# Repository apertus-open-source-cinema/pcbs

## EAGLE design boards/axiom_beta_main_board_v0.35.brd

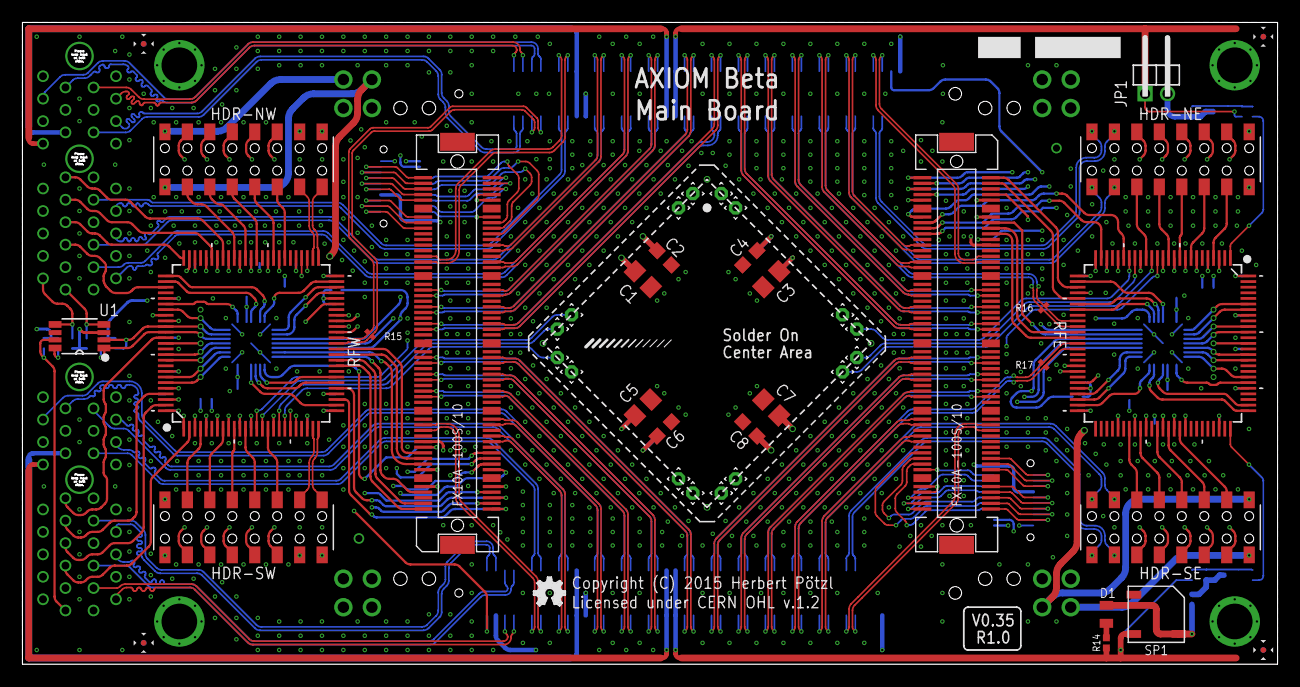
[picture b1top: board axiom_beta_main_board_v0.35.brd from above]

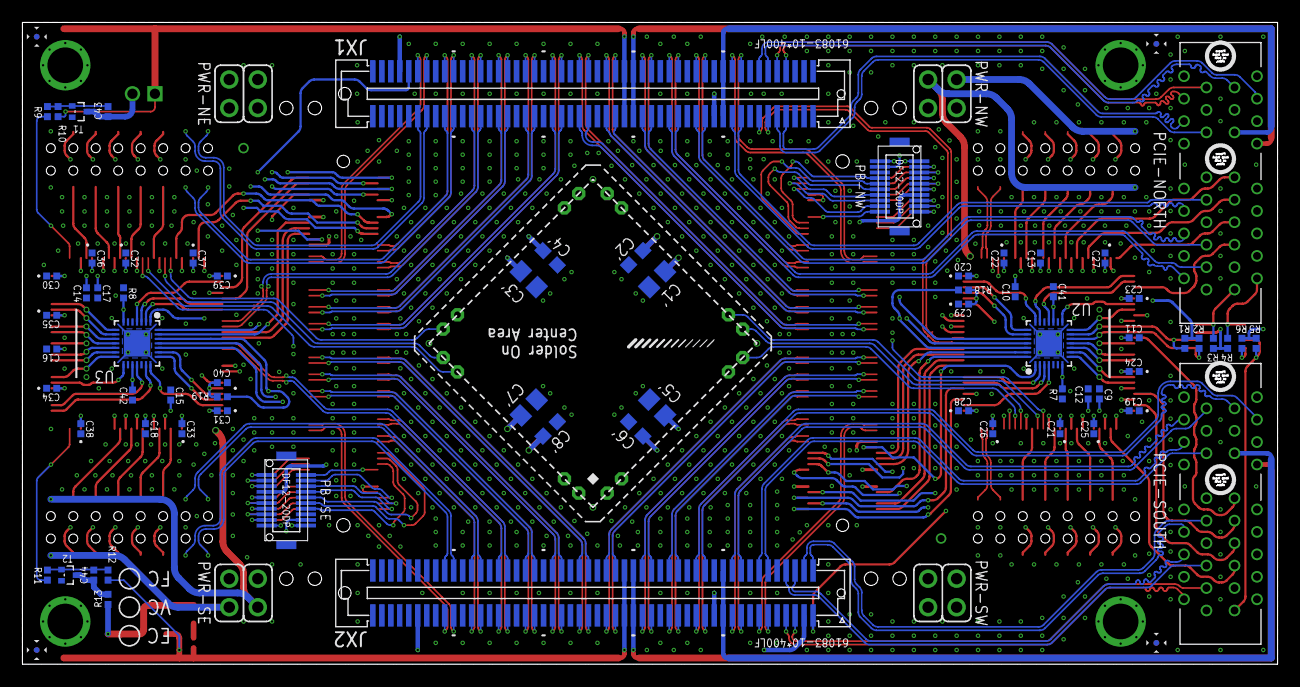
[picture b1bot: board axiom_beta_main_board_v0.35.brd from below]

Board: 4 copper layers, 111.8 x 57.1 mm, 113 parts (72 on the bottom side), 324 nets.

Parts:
C1, C1', C3, C3', C5, C5', C7, C7': 0805-A
C2, C2', C4, C4', C6, C6', C8, C8': 0603-A
C9, C10, C11, C12, C13, C14, C15, C16, C17, C18, C41, C42: 100n; 0402-B
C19, C20, C21, C22, C23, C24, C25, C26, C27, C28, C29, C30, C31, C32, C33, C34, C35, C36, C37, C38, C39, C40, C43, C44: 10n; 0402-B
D1: MICROMELF-R
HDR-NE: 62101621821
HDR-NW: 62101621821
HDR-SE: 62101621821
HDR-SW: 62101621821
JP1: 1X02M/90-S
LOGO1: OSHW_LOGO_FILLX0100-NT; OSHW_FILLX100_NOTEXT
PAD1, PAD2, PAD3, PAD4, PAD5, PAD6, PAD7, PAD8, PAD9, PAD10, PAD11, PAD12, PAD13, PAD14, PAD15, PAD16: PINPAD1.27MM; 1.2/0.6
PB-NW: DF12(XX)-20DP-0.5V
PB-SE: DF12(XX)-20DP-0.5V
PCIE-NORTH: PCIE-36-AXIOM-NOPEG; PCIE-36-NOPEG
PCIE-SOUTH: PCIE-36-AXIOM-NOPEG; PCIE-36-NOPEG
PWR-NE: PINHD-2X02_2.54; 2X02
PWR-NW: PINHD-2X02_2.54; 2X02
PWR-SE: PINHD-2X02_2.54; 2X02
PWR-SW: PINHD-2X02_2.54; 2X02
R1, R2, R3, R4, R5, R6: 4k7; 0402-B
R7, R8: 50R; 0402-B
R9, R10, R11, R12, R13, R14: 0402-B
R15, R16, R17: 100R; 0201-B
R18, R19: 10k; 0402-B
RFE: MACHXO2-100; MACHXO2-100TQFP
RFW: MACHXO2-100; MACHXO2-100TQFP
SP1: KSSG23J12
T1, T2: NX3008NBKT; SOT416
U1: PCA9540BDP; SOP65P490X300-8N
U2, U3: PIC16F1718-I/MV; QFN40P400X400X55-29N
X-EAST: FX10-100/10S; FX10A-100S/10
X-WEST: FX10-100/10S; FX10A-100S/10
ZED1: µZ-FCI-NOHOLES-R; µZ-NOHOLES-R

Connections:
!E_RESET!: U3.1, X-EAST.19
!SS!_E: RFE.27, U3.4
!SS!_W: RFW.27, U2.4
!W_RESET!: U2.1, X-WEST.19
A_!RST: PB-NW.2, R18.2, U2.26
A_SCL: PB-NW.1, U2.24
A_SDA: PB-NW.3, U2.25
BANK13_00_N: PCIE-NORTH.B17, ZED1.89
BANK13_00_P: PCIE-NORTH.B16, ZED1.87
BANK13_01_N: R15.2, RFW.38, ZED1.90
BANK13_01_P: R15.1, RFW.39, ZED1.88
BANK13_02_N: PCIE-NORTH.A16, ZED1.93
BANK13_02_P: PCIE-NORTH.A17, ZED1.91
BANK13_03_N: PCIE-NORTH.A14, ZED1.94
BANK13_03_P: PCIE-NORTH.A13, ZED1.92
BANK13_04_N: PCIE-SOUTH.A6, ZED1.195
BANK13_04_P: PCIE-SOUTH.A5, ZED1.193
BANK13_05_N: PCIE-SOUTH.A3, ZED1.196
BANK13_05_P: PCIE-SOUTH.A2, ZED1.194
BANK13_06_N: PCIE-SOUTH.A8, ZED1.199
BANK13_06_P: PCIE-SOUTH.A9, ZED1.197
BANK13_SE_0: R7.1, RFW.88, U2.7, ZED1.200
B_!RST: PB-SE.2, R19.2, U3.26
B_SCL: PB-SE.1, U3.24
B_SDA: PB-SE.3, U3.25
CSO_NE_V: C3.1, C3'.1, C4.1, C4'.1, PAD2.1, ZED1.7
CSO_NW_V: C1.1, C1'.1, C2.1, C2'.1, PAD15.1, PWR-NW.1
CSO_SE_V: C7.1, C7'.1, C8.1, C8'.1, PAD7.1, PWR-SE.1
CSO_SW_V: C5.1, C5'.1, C6.1, C6'.1, PAD10.1, ZED1.112
C_CK_E: PAD5.1, RFE.18
C_CK_W: PAD13.1, RFW.18
C_EN_E: PAD3.1, RFE.14
C_EN_W: PAD11.1, RFW.14
C_SI_E: PAD4.1, RFE.19
C_SI_W: PAD12.1, RFW.19
C_SO_E: PAD6.1, RFE.15
C_SO_W: PAD14.1, RFW.15
DONE_E: RFE.76, U3.20
DONE_W: RFW.76, U2.20
E_EN: RFE.20, X-EAST.14
E_I2C_EN: U3.27, X-EAST.13
E_I2C_V: PWR-NE.1, X-EAST.11
E_SCK: RFE.21, X-EAST.12
E_SCL: RFE.36, X-EAST.15
E_SDA: RFE.37, X-EAST.17
E_SDI: RFE.24, X-EAST.16
E_SDO: RFE.25, X-EAST.18
E_SPI_V: PWR-NE.3, X-EAST.21
E_VE_CV: PB-SE.19, X-EAST.90
E_VE_OV: PB-SE.10, X-EAST.93
E_VE_UV: PB-SE.12, X-EAST.91
GND: C1.2, C1'.2, C2.2, C2'.2, C3.2, C3'.2, C4.2, C4'.2, C5.2, C5'.2, C6.2, C6'.2, C7.2, C7'.2, C8.2, C8'.2, C9.2, C10.2, C11.2, C12.2, C13.2, C14.2, C15.2, C16.2, C17.2, C18.2, C19.2, C20.2, C21.2, C22.2, C23.2, C24.2, C25.2, C26.2, C27.2, C28.2, C29.2, C30.2, C31.2, C32.2, C33.2, C34.2, C35.2, C36.2, C37.2, C38.2, C39.2, C40.2, C41.2, C42.2, HDR-NE.1, HDR-NE.2, HDR-SW.1, HDR-SW.2, PAD1.1, PAD8.1, PAD9.1, PAD16.1, PB-NW.5, PB-SE.5, PCIE-NORTH.A1, PCIE-NORTH.A4, PCIE-NORTH.A7, PCIE-NORTH.A10, PCIE-NORTH.A12, PCIE-NORTH.A15, PCIE-NORTH.A18, PCIE-NORTH.B15, PCIE-NORTH.B18, PCIE-SOUTH.A1, PCIE-SOUTH.A4, PCIE-SOUTH.A7, PCIE-SOUTH.A10, PCIE-SOUTH.A12, PCIE-SOUTH.A15, PCIE-SOUTH.A18, PCIE-SOUTH.B15, PCIE-SOUTH.B18, R7.2, R8.2, RFE.6, RFE.22, RFE.33, RFE.44, RFE.56, RFE.72, RFE.79, RFE.92, RFW.6, RFW.22, RFW.33, RFW.44, RFW.56, RFW.72, RFW.79, RFW.92, T1.2, U1.6, U2.5, U2.16, U2.29, U3.5, U3.16, U3.29, X-EAST.5, X-EAST.20, X-EAST.23, X-EAST.26, X-EAST.29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
INITN_E: RFE.77, U3.18
INITN_W: RFW.77, U2.18
IO_SCL: RFE.86, U3.12
IO_SDA: RFE.85, U3.13
JTAGENB_E: RFE.82, U3.14
JTAGENB_W: RFW.82, U2.14
JTAG_V: PWR-SW.3, X-WEST.21
JX1_00_N: X-EAST.27, ZED1.13
JX1_00_P: X-EAST.25, ZED1.11
JX1_01_N: HDR-NE.13, ZED1.14
JX1_01_P: HDR-NE.15, ZED1.12
JX1_02_N: X-EAST.24, ZED1.19
JX1_02_P: X-EAST.22, ZED1.17
JX1_03_N: HDR-NE.14, ZED1.20
JX1_03_P: HDR-NE.16, ZED1.18
JX1_04_N: X-EAST.30, ZED1.25
JX1_04_P: X-EAST.28, ZED1.23
JX1_05_N: R16.2, RFE.35, ZED1.26
JX1_05_P: R16.1, RFE.34, ZED1.24
JX1_06_N: X-EAST.36, ZED1.31
JX1_06_P: X-EAST.34, ZED1.29
JX1_07_N: X-EAST.35, ZED1.32
JX1_07_P: X-EAST.33, ZED1.30
JX1_08_N: X-EAST.42, ZED1.37
JX1_08_P: X-EAST.40, ZED1.35
JX1_09_N: X-EAST.41, ZED1.38
JX1_09_P: X-EAST.39, ZED1.36
JX1_10_N: X-EAST.48, ZED1.43
JX1_10_P: X-EAST.46, ZED1.41
JX1_11_N: X-EAST.47, ZED1.44
JX1_11_P: X-EAST.45, ZED1.42
JX1_12_N: X-WEST.56, ZED1.49
JX1_12_P: X-WEST.54, ZED1.47
JX1_13_N: X-WEST.55, ZED1.50
JX1_13_P: X-WEST.53, ZED1.48
JX1_14_N: X-WEST.62, ZED1.55
JX1_14_P: X-WEST.60, ZED1.53
JX1_15_N: X-WEST.61, ZED1.56
JX1_15_P: X-WEST.59, ZED1.54
JX1_16_N: X-WEST.68, ZED1.63
JX1_16_P: X-WEST.66, ZED1.61
JX1_17_N: X-WEST.67, ZED1.64
JX1_17_P: X-WEST.65, ZED1.62
JX1_18_N: X-WEST.74, ZED1.69
JX1_18_P: X-WEST.72, ZED1.67
JX1_19_N: PCIE-NORTH.A3, ZED1.70
JX1_19_P: PCIE-NORTH.A2, ZED1.68
JX1_20_N: X-WEST.80, ZED1.75
JX1_20_P: X-WEST.78, ZED1.73
JX1_21_N: PCIE-NORTH.A6, ZED1.76
JX1_21_P: PCIE-NORTH.A5, ZED1.74
JX1_22_N: X-WEST.75, ZED1.83
JX1_22_P: X-WEST.73, ZED1.81
JX1_23_N: PCIE-NORTH.A9, ZED1.84
JX1_23_P: PCIE-NORTH.A8, ZED1.82
JX1_SE_0: R8.1, RFE.88, U3.7, ZED1.9
JX2_00_N: HDR-SE.14, ZED1.119
JX2_00_P: HDR-SE.16, ZED1.117
JX2_01_N: X-EAST.73, ZED1.120
JX2_01_P: X-EAST.75, ZED1.118
JX2_02_N: HDR-SE.13, ZED1.125
JX2_02_P: HDR-SE.15, ZED1.123
JX2_03_N: X-EAST.78, ZED1.126
JX2_03_P: X-EAST.80, ZED1.124
JX2_04_N: R17.1, RFE.38, ZED1.131
JX2_04_P: R17.2, RFE.39, ZED1.129
JX2_05_N: X-EAST.72, ZED1.132
JX2_05_P: X-EAST.74, ZED1.130
JX2_06_N: X-EAST.65, ZED1.137
JX2_06_P: X-EAST.67, ZED1.135
JX2_07_N: X-EAST.66, ZED1.138
JX2_07_P: X-EAST.68, ZED1.136
JX2_08_N: X-EAST.59, ZED1.143
JX2_08_P: X-EAST.61, ZED1.141
JX2_09_N: X-EAST.60, ZED1.144
JX2_09_P: X-EAST.62, ZED1.142
JX2_10_N: X-EAST.53, ZED1.149
JX2_10_P: X-EAST.55, ZED1.147
JX2_11_N: X-EAST.54, ZED1.150
JX2_11_P: X-EAST.56, ZED1.148
JX2_12_N: X-WEST.45, ZED1.155
JX2_12_P: X-WEST.47, ZED1.153
JX2_13_N: X-WEST.46, ZED1.156
JX2_13_P: X-WEST.48, ZED1.154
JX2_14_N: X-WEST.39, ZED1.163
JX2_14_P: X-WEST.41, ZED1.161
JX2_15_N: X-WEST.40, ZED1.164
JX2_15_P: X-WEST.42, ZED1.162
JX2_16_N: X-WEST.33, ZED1.169
JX2_16_P: X-WEST.35, ZED1.167
JX2_17_N: X-WEST.34, ZED1.170
JX2_17_P: X-WEST.36, ZED1.168
JX2_18_N: PCIE-SOUTH.B17, ZED1.175
JX2_18_P: PCIE-SOUTH.B16, ZED1.173
JX2_19_N: X-WEST.28, ZED1.176
JX2_19_P: X-WEST.30, ZED1.174
JX2_20_N: PCIE-SOUTH.A17, ZED1.183
JX2_20_P: PCIE-SOUTH.A16, ZED1.181
JX2_21_N: X-WEST.22, ZED1.184
JX2_21_P: X-WEST.24, ZED1.182
JX2_22_N: PCIE-SOUTH.A13, ZED1.189
JX2_22_P: PCIE-SOUTH.A14, ZED1.187
JX2_23_N: X-WEST.25, ZED1.190
JX2_23_P: X-WEST.27, ZED1.188
unnamed: C43.2, JP1.2, T1.3
unnamed: C44.2, R13.1, T2.3
unnamed: D1.C, R14.1
unnamed: D1.A, R13.2, SP1.2
unnamed: C43.1, R9.2, R10.2, T1.1
unnamed: C44.1, R11.1, R12.2, T2.1
N_CHK_V: PB-NW.14, X-WEST.92
N_I2C_EN: U3.28, X-EAST.7
N_I2C_V: PWR-NE.4, X-EAST.9
N_IO0: R9.1, RFE.1
N_SCK: RFE.42, X-EAST.2
N_SCL: RFE.28, X-EAST.1
N_SDA: RFE.30, X-EAST.3
N_SDI: RFE.29, X-EAST.6
N_SDO: RFE.43, X-EAST.4
N_SPI_EN: RFE.45, X-EAST.8
N_SPI_V: PWR-NE.2, X-EAST.10
N_VE_CV: PB-NW.17, X-WEST.96
N_VE_OV: PB-NW.8, X-WEST.95
N_VE_RS: PB-NW.7, X-WEST.88
N_VE_UV: PB-NW.20, X-WEST.85
N_VN_CV: PB-NW.15, X-WEST.98
N_VN_OV: PB-NW.6, X-WEST.97
N_VN_RS: PB-NW.11, X-WEST.86
N_VN_UV: PB-NW.18, X-WEST.87
N_VW_CV: PB-NW.13, X-WEST.100
N_VW_OV: PB-NW.4, X-WEST.99
N_VW_RS: PB-NW.9, X-WEST.84
N_VW_UV: PB-NW.16, X-WEST.89
PB22B_E: RFE.47, U3.23
PB22B_W: RFW.47, U2.23
PCIE_I2C_V: PCIE-NORTH.B3, PCIE-SOUTH.B3, R3.1, R4.1, R5.1, R6.1, U1.3, ZED1.198
PCIE_N_5V: PCIE-NORTH.B12, ZED1.59, ZED1.60
PCIE_N_IO0: PCIE-NORTH.B4, RFW.83
PCIE_N_IO1: PCIE-NORTH.B5, RFW.78
PCIE_N_IO2: PCIE-NORTH.B6, RFW.74
PCIE_N_IO3: PCIE-NORTH.B7, RFW.75
PCIE_N_IO4: PCIE-NORTH.B8, RFW.71
PCIE_N_IO5: PCIE-NORTH.B9, RFW.70
PCIE_N_IO6: PCIE-NORTH.B10, RFW.69
PCIE_N_IO7: PCIE-NORTH.B11, RFW.68
PCIE_N_SCL: PCIE-NORTH.B2, R4.2, U1.5
PCIE_N_SDA: PCIE-NORTH.B1, R3.2, U1.4
PCIE_N_V: PCIE-NORTH.B13, ZED1.79, ZED1.80
PCIE_N_VCCIO: PCIE-NORTH.B14, ZED1.78
PCIE_SCL: R2.2, RFW.86, U1.1, U2.12
PCIE_SDA: R1.2, RFW.85, U1.2, U2.13
PCIE_S_5V: PCIE-SOUTH.B12, ZED1.159, ZED1.160
PCIE_S_IO0: PCIE-SOUTH.B4, RFW.1
PCIE_S_IO1: PCIE-SOUTH.B5, RFW.2
PCIE_S_IO2: PCIE-SOUTH.B6, RFW.98
PCIE_S_IO3: PCIE-SOUTH.B7, RFW.99
PCIE_S_IO4: PCIE-SOUTH.B8, RFW.96
PCIE_S_IO5: PCIE-SOUTH.B9, RFW.97
PCIE_S_IO6: PCIE-SOUTH.B10, RFW.84
PCIE_S_IO7: PCIE-SOUTH.B11, RFW.87
PCIE_S_SCL: PCIE-SOUTH.B2, R6.2, U1.8
PCIE_S_SDA: PCIE-SOUTH.B1, R5.2, U1.7
PCIE_S_V: PCIE-SOUTH.B13, ZED1.179, ZED1.180
PCIE_S_VCCIO: PCIE-SOUTH.B14, ZED1.178
PEX_N_V: JP1.1, R10.1, ZED1.57, ZED1.58
PEX_S_V: R12.1, R14.2, SP1.1, ZED1.157, ZED1.158
PROGRAMN_E: RFE.81, U3.15
PROGRAMN_W: RFW.81, U2.15
RFAB_E_V: C14.1, C15.1, C30.1, C31.1, PWR-SE.3, RFE.50, RFE.100
RFAB_W_V: C9.1, C10.1, C19.1, C20.1, PWR-NW.3, RFW.50, RFW.100
SCK_E: RFE.31, U3.3
SCK_W: RFW.31, U2.3
SDI_E: RFE.49, U3.21
SDI_W: RFW.49, U2.21
SDO_E: RFE.32, U3.2
SDO_W: RFW.32, U2.2
SH_NE_IO0: HDR-NE.4, RFE.4
SH_NE_IO1: HDR-NE.3, RFE.3
SH_NE_IO2: HDR-NE.6, RFE.8
SH_NE_IO3: HDR-NE.5, RFE.7
SH_NE_IO4: HDR-NE.8, RFE.10
SH_NE_IO5: HDR-NE.7, RFE.9
SH_NE_IO6: HDR-NE.10, RFE.12
SH_NE_IO7: HDR-NE.9, RFE.13
SH_NE_IO8: HDR-NE.12, RFE.16
SH_NE_IO9: HDR-NE.11, RFE.17
SH_NW_IO0: HDR-NW.4, RFW.67
SH_NW_IO1: HDR-NW.3, RFW.66
SH_NW_IO2: HDR-NW.6, RFW.65
SH_NW_IO3: HDR-NW.5, RFW.64
SH_NW_IO4: HDR-NW.8, RFW.63
SH_NW_IO5: HDR-NW.7, RFW.62
SH_NW_IO6: HDR-NW.10, RFW.60
SH_NW_IO7: HDR-NW.9, RFW.59
SH_NW_IO8: HDR-NW.12, RFW.58
SH_NW_IO9: HDR-NW.11, RFW.57
SH_NW_V: HDR-NW.2, PWR-NW.4
SH_NW_VIO: C11.1, C12.1, C13.1, C21.1, C22.1, C23.1, C24.1, C25.1, C26.1, C27.1, C28.1, C29.1, C41.1, HDR-NW.1, PWR-NW.2, R1.1, R2.1, R18.1, RFW.5, RFW.11, RFW.23, RFW.26, RFW.46, RFW.55, RFW.73, RFW.80, RFW.93, U2.17
SH_SE_IO0: HDR-SE.4, RFE.67
SH_SE_IO1: HDR-SE.3, RFE.66
SH_SE_IO2: HDR-SE.6, RFE.65
SH_SE_IO3: HDR-SE.5, RFE.64
SH_SE_IO4: HDR-SE.8, RFE.63
SH_SE_IO5: HDR-SE.7, RFE.62
SH_SE_IO6: HDR-SE.10, RFE.60
SH_SE_IO7: HDR-SE.9, RFE.59
SH_SE_IO8: HDR-SE.12, RFE.58
SH_SE_IO9: HDR-SE.11, RFE.57
SH_SE_V: HDR-SE.2, PWR-SE.4
SH_SE_VIO: C16.1, C17.1, C18.1, C32.1, C33.1, C34.1, C35.1, C36.1, C37.1, C38.1, C39.1, C40.1, C42.1, HDR-SE.1, PWR-SE.2, R19.1, RFE.5, RFE.11, RFE.23, RFE.26, RFE.46, RFE.55, RFE.73, RFE.80, RFE.93, U3.17
SH_SW_IO0: HDR-SW.4, RFW.4
SH_SW_IO1: HDR-SW.3, RFW.3
SH_SW_IO2: HDR-SW.6, RFW.8
SH_SW_IO3: HDR-SW.5, RFW.7
SH_SW_IO4: HDR-SW.8, RFW.10
SH_SW_IO5: HDR-SW.7, RFW.9
SH_SW_IO6: HDR-SW.10, RFW.12
SH_SW_IO7: HDR-SW.9, RFW.13
SH_SW_IO8: HDR-SW.12, RFW.16
SH_SW_IO9: HDR-SW.11, RFW.17
SN_E: RFE.48, U3.22
SN_W: RFW.48, U2.22
S_CHK_V: PB-SE.14, X-EAST.92
S_I2C_EN: U2.28, X-WEST.7
S_I2C_V: PWR-SW.4, X-WEST.9
S_IO0: R11.2, RFE.75
S_SCK: RFW.28, X-WEST.2
S_SCL: RFW.34, X-WEST.1
S_SDA: RFW.35, X-WEST.3
S_SDI: RFW.30, X-WEST.6
S_SDO: RFW.29, X-WEST.4
S_SPI_EN: RFW.45, X-WEST.8
S_SPI_V: PWR-SW.2, X-WEST.10
S_VE_CV: PB-SE.13, X-EAST.100
S_VE_OV: PB-SE.4, X-EAST.99
S_VE_RS: PB-SE.9, X-EAST.84
S_VE_UV: PB-SE.16, X-EAST.89
S_VS_CV: PB-SE.15, X-EAST.98
S_VS_OV: PB-SE.6, X-EAST.97
S_VS_RS: PB-SE.11, X-EAST.86
S_VS_UV: PB-SE.18, X-EAST.87
S_VW_CV: PB-SE.17, X-EAST.96
S_VW_OV: PB-SE.8, X-EAST.95
S_VW_RS: PB-SE.7, X-EAST.88
S_VW_UV: PB-SE.20, X-EAST.85
TCK: RFW.43, X-WEST.12
TCK_E: RFE.91, U3.10
TCK_W: RFW.91, U2.10
TDI: RFW.41, X-WEST.16
TDI_E: RFE.94, U3.9
TDI_W: RFW.94, U2.9
TDO: RFW.40, X-WEST.18
TDO_E: RFE.95, U3.8
TDO_W: RFW.95, U2.8
TMS: RFW.42, X-WEST.14
TMS_E: RFE.90, U3.11
TMS_W: RFW.90, U2.11
W_I2C_EN: U2.27, X-WEST.13
W_I2C_V: PWR-SW.1, X-WEST.11
W_SCL: RFW.36, X-WEST.15
W_SDA: RFW.37, X-WEST.17
W_VW_CV: PB-NW.19, X-WEST.90
W_VW_OV: PB-NW.10, X-WEST.93
W_VW_UV: PB-NW.12, X-WEST.91
XX1_N: HDR-NW.13, RFW.52
XX1_P: HDR-NW.15, RFW.51
XX2_N: HDR-NW.14, RFW.54
XX2_P: HDR-NW.16, RFW.53
XX3_N: HDR-SW.16, RFW.25
XX3_P: HDR-SW.14, RFW.24
XX4_N: HDR-SW.15, RFW.21
XX4_P: HDR-SW.13, RFW.20

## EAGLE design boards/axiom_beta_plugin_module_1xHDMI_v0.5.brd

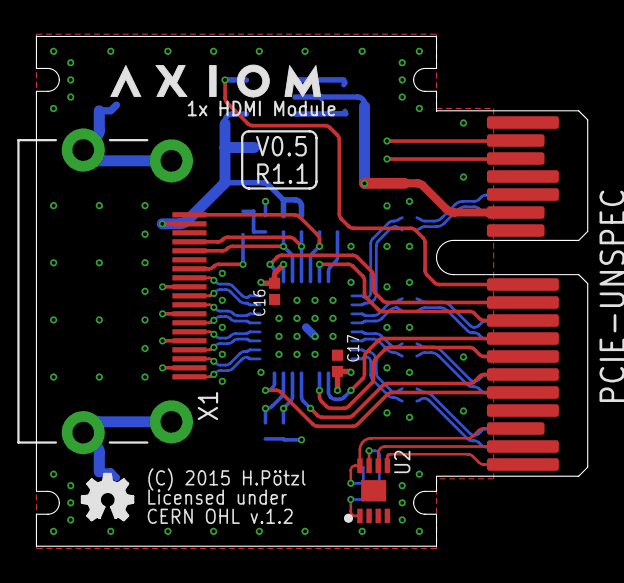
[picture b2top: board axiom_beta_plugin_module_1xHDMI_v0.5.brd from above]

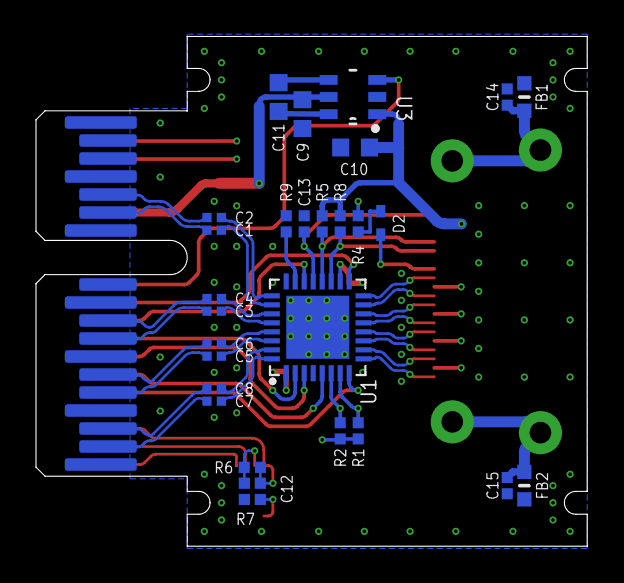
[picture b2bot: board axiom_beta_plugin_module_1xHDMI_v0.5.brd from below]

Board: 4 copper layers, 30.6 x 28.3 mm, 35 parts (28 on the bottom side), 50 nets.

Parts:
C1, C2, C3, C4, C5, C6, C7, C8: 100n; 0402-C
C9, C10, C11: 0603-B
C12: 0402-B
C13: 1-10n; 0402-B
C14, C15: 10n; 0402-B
C16, C17: 100n; 0402-B
D2: SOD523
FB1, FB2: _0603MP
LOGO2: OSHW_LOGO_FILLX0100-NT; OSHW_FILLX100_NOTEXT
PCIE-UNSPEC: PCIE-36-AXIOM
R1, R2, R5, R8: 2k2; 0402-B
R4, R6, R7: 0402-B
R9: 12k4; 0402-B
U1: PTN3363; HVQFN32
U2: BR24G04NUX; DFN200X300X100-9N
U3: REG710-DBV; DBV
U$1: AXIOM_LOGO459X70; AXIOM_LOGO_459X70
X1: HDMI-10029449; 10029449-X01XLF

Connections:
3V3: C9.1, C16.1, C17.1, PCIE-UNSPEC.B13, R1.1, R2.1, R4.1, U1.1, U1.18, U3.5
5V0: C10.1, R5.1, R8.1, U3.1, X1.18
!OE!: PCIE-UNSPEC.B10, U1.17
CLOCK_N: U1.16, X1.12
CLOCK_P: U1.15, X1.10
DATA0_N: U1.14, X1.9
DATA0_P: U1.13, X1.7
DATA1_N: U1.12, X1.6
DATA1_P: U1.11, X1.4
DATA2_N: U1.10, X1.3
DATA2_P: U1.9, X1.1
DDC_EN: PCIE-UNSPEC.B9, U1.22
DDET: PCIE-UNSPEC.B7, U1.3
EN: PCIE-UNSPEC.B11, U3.3
EQ0: PCIE-UNSPEC.B5, U1.8
EQ1: PCIE-UNSPEC.B8, U1.2
GND: C9.2, C10.2, C12.2, C13.2, C14.2, C15.2, C16.2, C17.2, FB1.2, FB2.2, PCIE-UNSPEC.A1, PCIE-UNSPEC.A4, PCIE-UNSPEC.A7, PCIE-UNSPEC.A10, PCIE-UNSPEC.A12, PCIE-UNSPEC.A15, PCIE-UNSPEC.A18, PCIE-UNSPEC.B15, PCIE-UNSPEC.B18, R7.2, R9.2, U1.24, U1.EP, U2.1, U2.2, U2.3, U2.4, U2.EP, U3.2, X1.2, X1.5, X1.8, X1.11, X1.17
HDMI_CEC: D2.C, X1.13
HDMI_HP: C13.1, U1.21, X1.19
HDMI_SCL: R8.2, U1.19, X1.15
HDMI_SDA: R5.2, U1.20, X1.16
I2C_V: C12.1, PCIE-UNSPEC.B3, R6.1, U2.8
IHP: PCIE-UNSPEC.B6, U1.5
IN_D1_N: C2.1, U1.25
IN_D1_P: C1.1, U1.26
IN_D2_N: C4.1, U1.27
IN_D2_P: C3.1, U1.28
IN_D3_N: C6.1, U1.29
IN_D3_P: C5.1, U1.30
IN_D4_N: C8.1, U1.31
IN_D4_P: C7.1, U1.32
ISCL: PCIE-UNSPEC.B16, R1.2, U1.7
ISDA: PCIE-UNSPEC.B17, R2.2, U1.6
LVDS_0_N: C8.2, PCIE-UNSPEC.A3
LVDS_0_P: C7.2, PCIE-UNSPEC.A2
LVDS_1_N: C6.2, PCIE-UNSPEC.A6
LVDS_1_P: C5.2, PCIE-UNSPEC.A5
LVDS_2_N: C4.2, PCIE-UNSPEC.A9
LVDS_2_P: C3.2, PCIE-UNSPEC.A8
LVDS_3_N: C2.2, PCIE-UNSPEC.A14
LVDS_3_P: C1.2, PCIE-UNSPEC.A13
unnamed: C11.1, U3.6
unnamed: C11.2, U3.4
unnamed: C14.1, FB1.1, X1.Z1, X1.Z2
unnamed: R6.2, R7.1, U2.7
unnamed: C15.1, FB2.1, X1.Z3, X1.Z4
unnamed: R9.1, U1.23
unnamed: D2.A, R4.2
SCL: PCIE-UNSPEC.B2, U2.6
SDA: PCIE-UNSPEC.B1, U2.5

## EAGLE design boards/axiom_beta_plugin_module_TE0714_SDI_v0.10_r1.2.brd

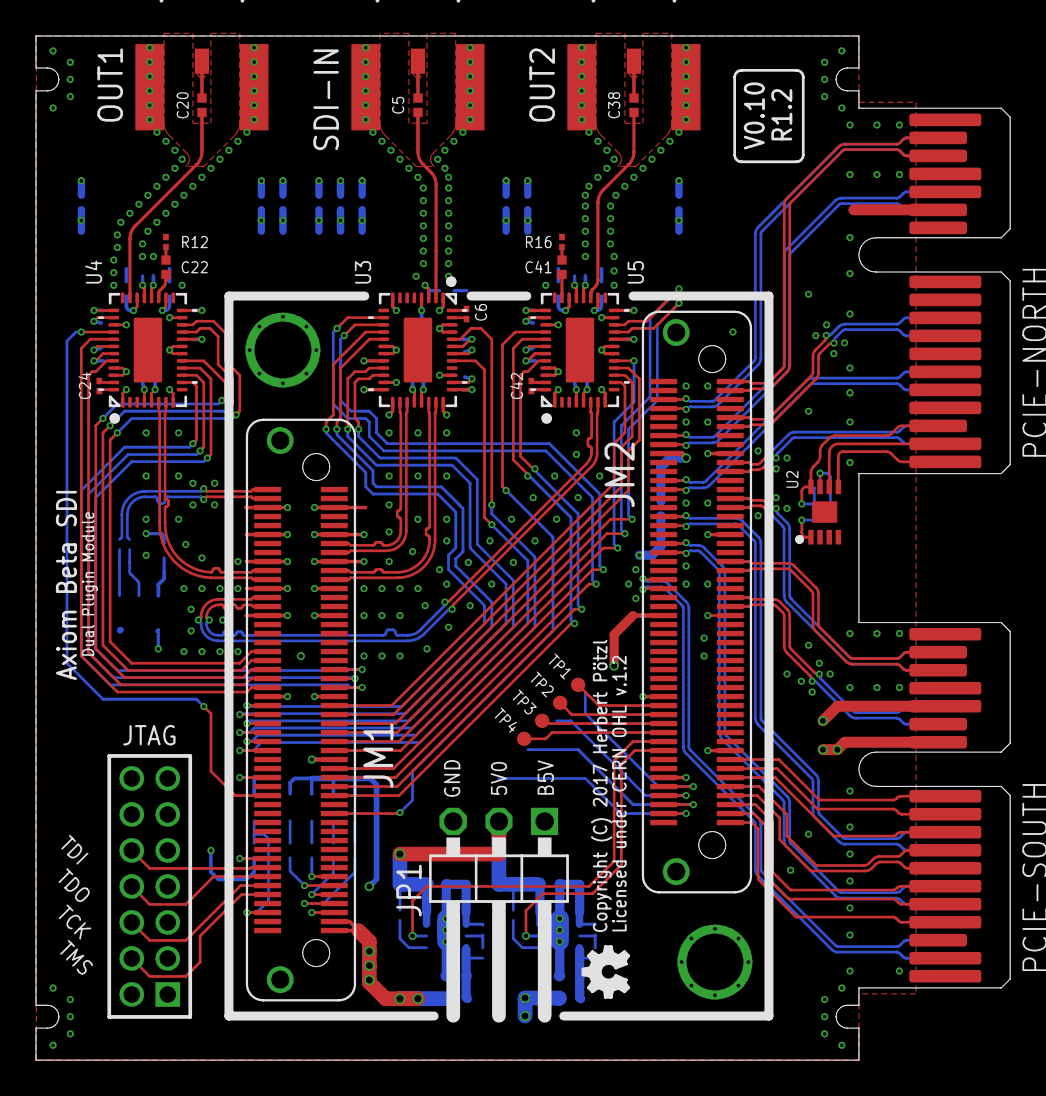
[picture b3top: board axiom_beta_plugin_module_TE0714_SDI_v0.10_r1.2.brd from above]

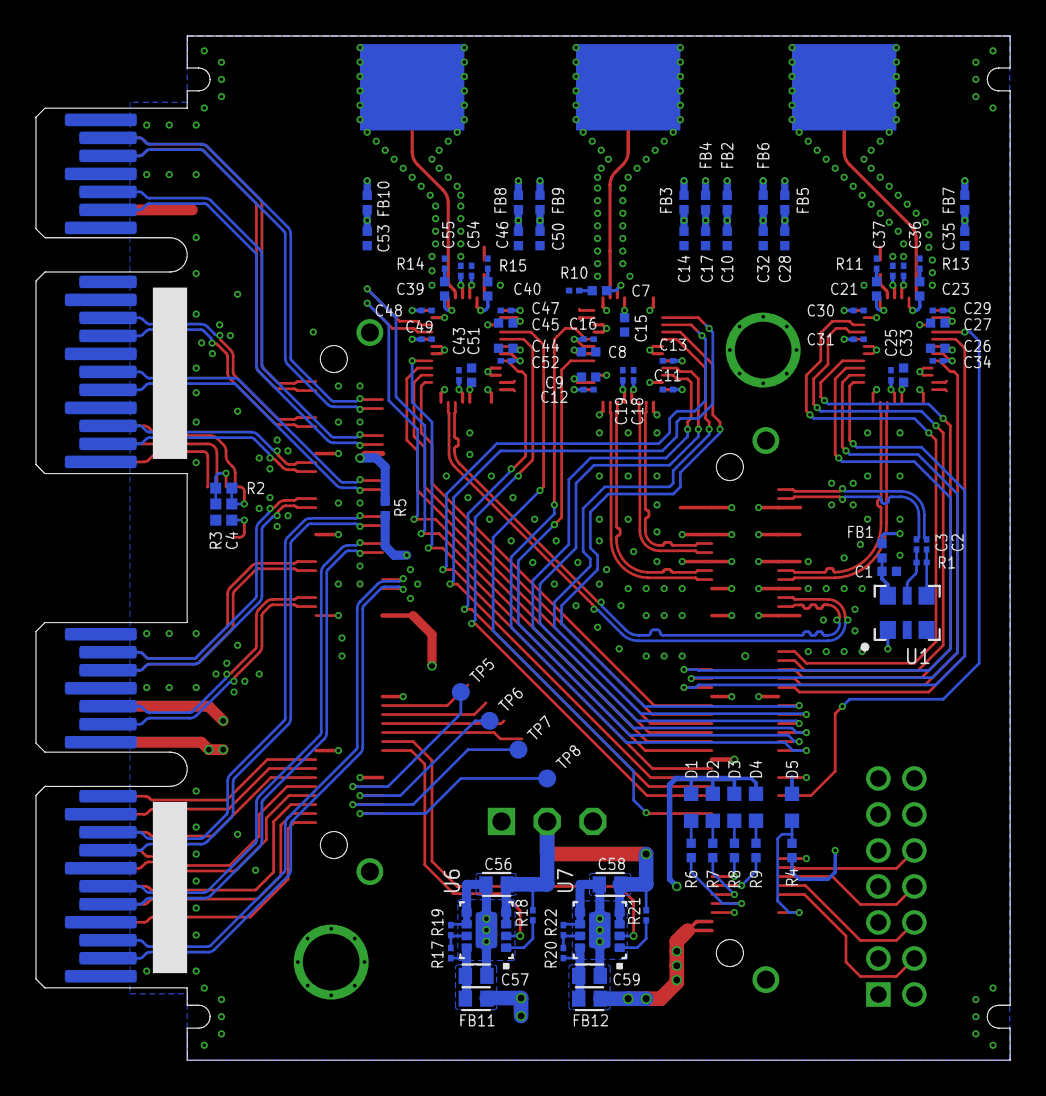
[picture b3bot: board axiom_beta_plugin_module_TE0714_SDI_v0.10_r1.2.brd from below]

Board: 4 copper layers, 54.1 x 56.9 mm, 123 parts (95 on the bottom side), 156 nets.

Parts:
C1: 470n; 0402-C
C2, C3, C11, C12, C13, C18, C19, C25, C29, C30, C31, C36, C37, C43, C47, C48, C49, C54, C55: 100n; 0201-C
C4: 0402-B
C5, C7, C20, C21, C22, C23, C38, C39, C40, C41: 4u7; 0402-C
C6, C24, C42: 470n; 0201-C
C8, C9, C10, C14, C15, C17, C26, C27, C28, C32, C33, C35, C44, C45, C46, C50, C51, C53: 10u; 0402-C
C16, C34, C52: 1u; 0201-C
C56, C57, C58, C59: 0603-C
D1, D2, D3, D4, D5: LED; CHIPLED_0603
FB1, FB2, FB3, FB4, FB5, FB6, FB7, FB8, FB9, FB10: 0402-C
FB11, FB12: 0603-C
JM1, JM2: LSHM-150-XX.X-XX-DV-A-S
JP1: 1X03/90-S
JTAG: 2X07M
LOGO2: OSHW_LOGO_FILLX0100-NT; OSHW_FILLX100_NOTEXT
OUT1, OUT2: HDBNC; HDBNC_EDGE_2SIDE
PCIE-NORTH: PCIE-36-AXIOM
PCIE-SOUTH: PCIE-36-AXIOM
R1: 100R; 0201-C
R2: 10k; 0402-B
R3: 1k; 0402-B
R4: 5k6; 0402-C
R5: DNP; 0402-C
R6, R7, R8, R9: 10k; 0402-C
R10: 0201-C
R11, R12, R13, R14, R15, R16: 75R; 0201-C
R17: 200k; 0201-C
R18, R21: 10k; 0201-C
R19, R22: 162k; 0201-C
R20: 510k; 0201-C
SDI-IN: HDBNC; HDBNC_EDGE_2SIDE
TP1, TP2, TP3, TP4: TPTP08R; TP08R
TP5, TP6, TP7, TP8: TPTP10R; TP10R
U1: DSC11XX-3.2X2.5; 3.2X2.5
U2: BR24G04NUX; DFN200X300X100-9N
U3: GS12241; UQFN40P600X400X100-41N
U4, U5: GS12281; UQFN40P600X400X100-41N
U6, U7: TPS82085; MICROSIP

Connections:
1V8: FB2.1, FB3.1, FB4.1, FB5.1, FB6.1, FB8.1, FB9.1, FB11.2, JM1.61, R5.1
3V3: D1.A, D2.A, D3.A, D4.A, FB1.1, FB7.1, FB10.1, FB12.2, JM1.97, JM1.99, R4.2
B14_L0: JM2.99, PCIE-SOUTH.B4
B14_L11_N: JM2.74, TP1.TP
B14_L11_P: JM2.76, TP2.TP
B14_L12_N: JM2.84, U6.2
B14_L12_P: JM2.82, U7.2
B14_L14_N: JM2.78, TP3.TP
B14_L14_P: JM2.80, TP4.TP
B14_L17_N: JM2.89, PCIE-SOUTH.B9
B14_L17_P: JM2.91, PCIE-SOUTH.B8
B14_L18_N: JM2.85, PCIE-SOUTH.B11
B14_L18_P: JM2.87, PCIE-SOUTH.B10
B14_L19_N: JM2.94, TP6.TP
B14_L19_P: JM2.92, TP5.TP
B14_L20_N: JM2.95, PCIE-SOUTH.B6
B14_L20_P: JM2.93, PCIE-SOUTH.B7
B14_L21_N: JM1.95, U1.1
B14_L21_P: JM1.93, R6.1
B14_L22_N: JM2.96, TP7.TP
B14_L22_P: JM2.98, TP8.TP
B14_L23_N: JM1.89, R9.1
B14_L23_P: JM1.91, R7.1
B14_L24_P: JM1.87, R8.1
B14_L25: JM2.97, PCIE-SOUTH.B5
B15_L1_N: JM2.14, PCIE-NORTH.A14
B15_L1_P: JM2.16, PCIE-NORTH.A13
B15_L5_N: JM2.8, PCIE-NORTH.A16
B15_L5_P: JM2.6, PCIE-NORTH.A17
B15_L6_N: JM2.26, PCIE-NORTH.A5
B15_L6_P: JM2.24, PCIE-NORTH.A6
B15_L7_N: JM2.1, PCIE-NORTH.B17
B15_L7_P: JM2.3, PCIE-NORTH.B16
B15_L10_N: JM2.11, PCIE-NORTH.A8
B15_L10_P: JM2.9, PCIE-NORTH.A9
B15_L12_N: JM2.34, PCIE-SOUTH.A8
B15_L12_P: JM2.32, PCIE-SOUTH.A9
B15_L13_N: JM2.38, PCIE-SOUTH.A6
B15_L13_P: JM2.40, PCIE-SOUTH.A5
B15_L15_N: JM2.19, PCIE-NORTH.A3
B15_L15_P: JM2.21, PCIE-NORTH.A2
B15_L18_N: JM2.27, PCIE-SOUTH.A17
B15_L18_P: JM2.29, PCIE-SOUTH.A16
B15_L19_N: JM2.41, PCIE-SOUTH.B17
B15_L19_P: JM2.43, PCIE-SOUTH.B16
B15_L22_N: JM2.46, PCIE-SOUTH.A3
B15_L22_P: JM2.48, PCIE-SOUTH.A2
B15_L23_N: JM2.51, PCIE-SOUTH.A13
B15_L23_P: JM2.49, PCIE-SOUTH.A14
B34_L3_N: JM1.42, U4.13
B34_L3_P: JM1.40, U4.17
B34_L4_N: JM1.41, U4.12
B34_L5_N: JM1.45, U4.10
B34_L5_P: JM1.43, U4.11
B34_L7_N: JM1.38, U4.18
B34_L8_N: JM1.52, U3.13
B34_L8_P: JM1.50, U3.12
B34_L9_N: JM1.46, U4.33
B34_L9_P: JM1.44, U4.36
B34_L10_N: JM1.51, U5.11
B34_L10_P: JM1.49, U5.10
B34_L11_N: JM1.53, U5.12
B34_L11_P: JM1.55, U5.17
B34_L12_N: JM1.57, U5.18
B34_L12_P: JM1.59, U5.13
B34_L13_N: JM1.56, U3.18
B34_L13_P: JM1.54, U3.17
B34_L14_N: JM1.60, U3.36
B34_L14_P: JM1.58, U3.33
B34_L16_P: JM1.70, U4.32
B34_L17_N: JM1.63, U3.11
B34_L17_P: JM1.65, U3.10
B34_L19_P: JM1.73, U5.32
B34_L21_N: JM1.69, U5.33
B34_L21_P: JM1.67, U5.36
DONE: D5.A, JM1.96, R4.1
EN_A: R18.1, U6.1
EN_B: R21.1, U7.1
FB_A: R17.1, R19.2, U6.7
FB_B: R20.1, R22.2, U7.7
GND: C1.2, C4.2, C8.2, C9.2, C10.2, C11.2, C12.2, C13.2, C14.2, C15.2, C16.2, C17.2, C18.2, C19.2, C25.2, C26.2, C27.2, C28.2, C29.2, C30.2, C31.2, C32.2, C33.2, C34.2, C35.2, C36.2, C37.2, C43.2, C44.2, C45.2, C46.2, C47.2, C48.2, C49.2, C50.2, C51.2, C52.2, C53.2, C54.2, C55.2, C56.2, C57.2, C58.2, C59.2, D5.C, JM1.5, JM1.6, JM1.11, JM1.12, JM1.17, JM1.18, JM1.23, JM1.24, JM1.29, JM1.30, JM1.47, JM1.48, JM1.66, JM1.84, JM1.98, JM1.100, JM1.F1, JM1.F2, JM2.17, JM2.35, JM2.36, JM2.72, JM2.83, JM2.90, JM2.F1, JM2.F2, JP1.3, JTAG.1, JTAG.3, JTAG.5, JTAG.7, JTAG.9, JTAG.11, JTAG.13, OUT1.2@1, OUT1.2@2, OUT1.2@3, OUT2.2@1, OUT2.2@2, OUT2.2@3, PCIE-NORTH.A1, PCIE-NORTH.A4, PCIE-NORTH.A7, PCIE-NORTH.A10, PCIE-NORTH.A12, PCIE-NORTH.A15, PCIE-NORTH.A18, PCIE-NORTH.B15, PCIE-NORTH.B18, PCIE-SOUTH.A1, PCIE-SOUTH.A4, PCIE-SOUTH.A7, PCIE-SOUTH.A10, PCIE-SOUTH.A12, PCIE-SOUTH.A15, PCIE-SOUTH.A18, PCIE-SOUTH.B15, PCIE-SOUTH.B18, R3.2, R10.2, R11.2, R12.2, R13.2, R14.2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
I2C_V: C4.1, PCIE-NORTH.B3, R2.1, U2.8
MGT_CLK0_N: C3.2, JM1.4
MGT_CLK0_P: C2.2, JM1.2
MGT_RX0_N: JM1.21, U3.27
MGT_RX0_P: JM1.19, U3.26
MGT_RX1_N: JM1.15, U3.23
MGT_RX1_P: JM1.13, U3.22
MGT_TX0_N: JM1.28, U5.6
MGT_TX0_P: JM1.26, U5.7
MGT_TX1_N: JM1.22, U4.6
MGT_TX1_P: JM1.20, U4.7
M_1V8: JM2.18, R5.2
unnamed: D1.C, R6.2
unnamed: D2.C, R7.2
unnamed: D3.C, R8.2
unnamed: D4.C, R9.2
unnamed: C6.2, U3.40
unnamed: C6.1, U3.39
unnamed: C24.2, U4.40
unnamed: C24.1, U4.39
unnamed: C9.1, U3.30
unnamed: C8.1, U3.34
unnamed: C21.2, R11.1
unnamed: C21.1, U4.22
unnamed: C22.1, U4.23
unnamed: C22.2, R12.1
unnamed: C23.1, U4.26
unnamed: C23.2, R13.1
unnamed: C7.2, R10.1
unnamed: C7.1, U3.3
unnamed: C27.1, U4.30
unnamed: C26.1, U4.34
unnamed: C20.1, U4.27
unnamed: C25.1, U4.5
unnamed: C20.2, OUT1.1
unnamed: C38.1, U5.23
unnamed: C5.2, U3.2
unnamed: C5.1, SDI-IN.1
unnamed: C38.2, OUT2.1
unnamed: C42.2, U5.40
unnamed: C43.1, U5.5
unnamed: C44.1, U5.34
unnamed: C45.1, U5.30
unnamed: C40.2, R15.1
unnamed: C40.1, U5.26
unnamed: C41.2, R16.1
unnamed: C41.1, U5.27
unnamed: C39.1, U5.22
unnamed: C39.2, R14.1
unnamed: C42.1, U5.39
unnamed: R2.2, R3.1, U2.7
OUT_N: C3.1, R1.2, U1.5
OUT_P: C2.1, R1.1, U1.4
SCL: PCIE-NORTH.B2, U2.6
SDA: PCIE-NORTH.B1, U2.5
S_5V: JP1.1, PCIE-SOUTH.B12
S_VCCIO: JM2.54, PCIE-SOUTH.B14
TCK: JM1.90, JTAG.6
TDI: JM1.86, JTAG.10
TDO: JM1.88, JTAG.8
TMS: JM1.92, JTAG.4
VCCIO0: JM2.53, JTAG.2
VCCO_4: C17.1, C18.1, C19.1, FB4.2, U3.24, U3.25
VCCO_8: C35.1, C36.1, C37.1, FB7.2, U4.24, U4.25
VCCO_9: C53.1, C54.1, C55.1, FB10.2, U5.24, U5.25
VCC_4: C14.1, C15.1, C16.1, FB3.2, U3.4, U3.35
VCC_8: C32.1, C33.1, C34.1, FB6.2, U4.4, U4.35
VCC_9: C50.1, C51.1, C52.1, FB9.2, U5.4, U5.35
VDD_4: C10.1, C11.1, C12.1, C13.1, FB2.2, U3.16, U3.20, U3.29
VDD_8: C28.1, C29.1, C30.1, C31.1, FB5.2, U4.16, U4.20, U4.29
VDD_9: C46.1, C47.1, C48.1, C49.1, FB8.2, U5.16, U5.20, U5.29
VOUT_A: C57.1, FB11.1, R17.2, U6.8
VOUT_B: C59.1, FB12.1, R20.2, U7.8
VSUP: C56.1, C58.1, JP1.2, R18.2, R21.2, U6.3, U6.4, U7.3, U7.4
V_CLK: C1.1, FB1.2, U1.6

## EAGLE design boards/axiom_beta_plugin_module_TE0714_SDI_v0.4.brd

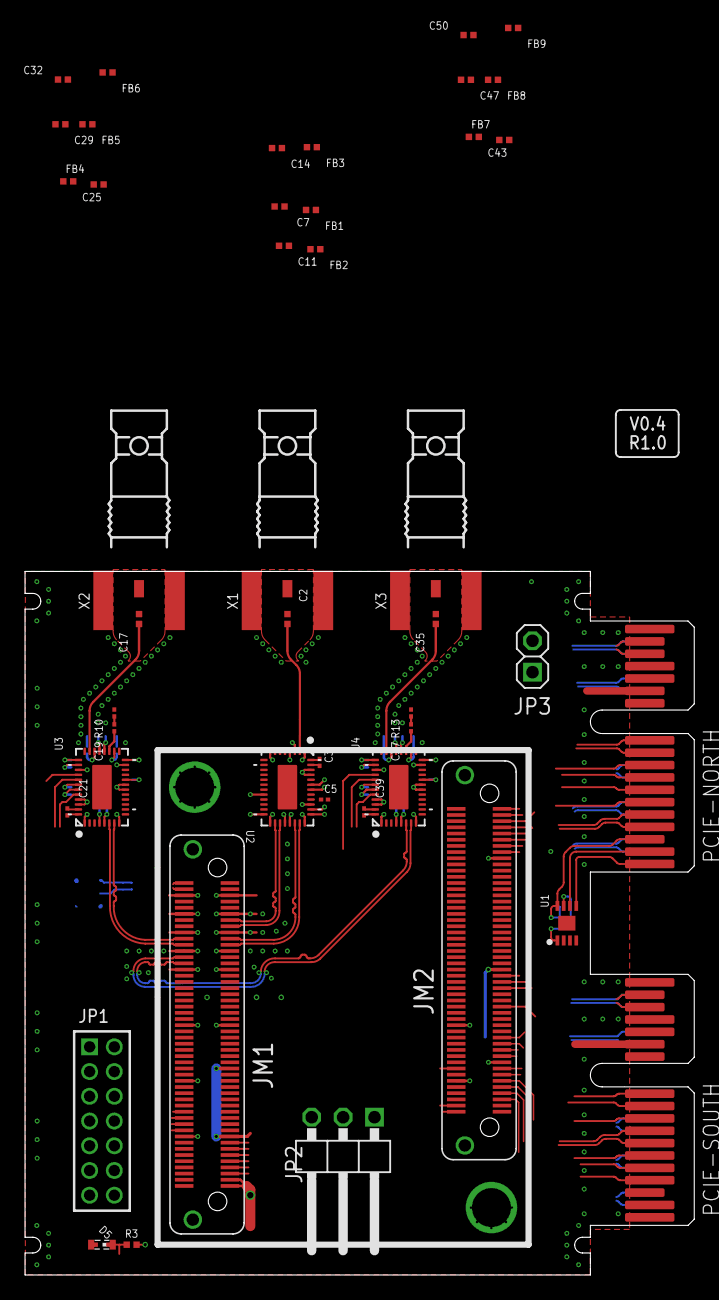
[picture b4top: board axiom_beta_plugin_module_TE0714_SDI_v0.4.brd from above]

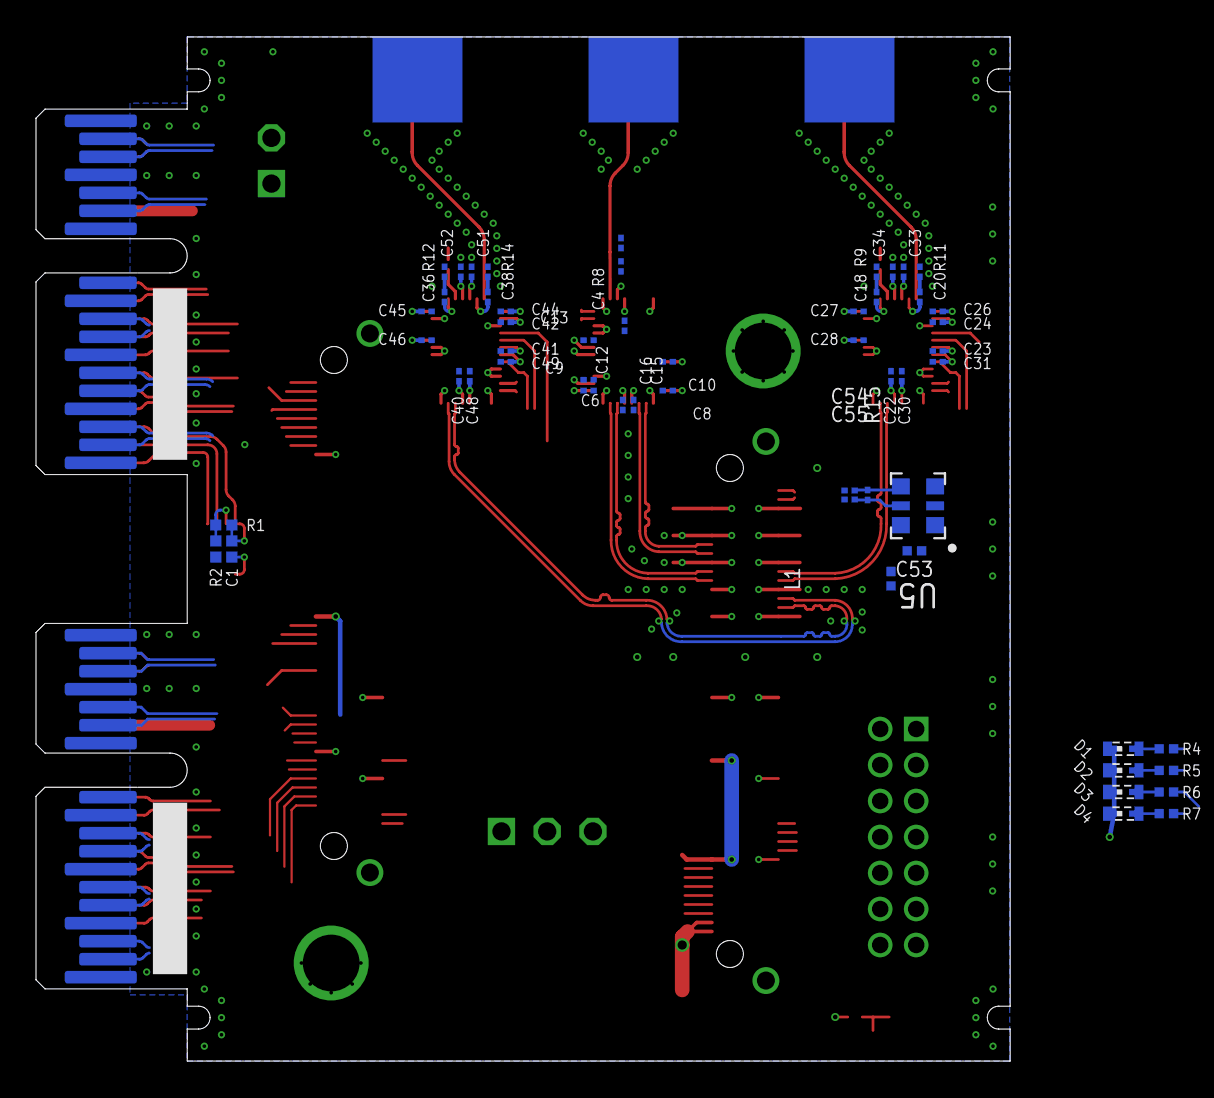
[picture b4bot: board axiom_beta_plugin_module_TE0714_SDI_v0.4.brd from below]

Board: 4 copper layers, 54.1 x 56.9 mm, 101 parts (56 on the bottom side), 73 nets.

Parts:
C1: 0402-B
C2, C17, C35: 4u7; 0402-C
C3, C21, C39: 470n; 0201-C
C4, C18, C19, C20, C36, C37, C38: 4u7; 0201-C
C5, C6, C12, C23, C24, C30, C41, C42, C48: 10u; 0201-C
C7, C11, C14, C25, C29, C32, C43, C47, C50: 10u; 0402-C
C8, C9, C10, C15, C16, C22, C26, C27, C28, C33, C34, C40, C44, C45, C46, C51, C52, C54, C55: 100n; 0201-C
C13, C31, C49: 1u; 0201-C
C53: 470n; 0402-C
D1, D2, D3, D4, D5: SMARTLED-TTW
FB1, FB2, FB3, FB4, FB5, FB6, FB7, FB8, FB9: 0402-C
JM1, JM2: LSHM-150-XX.X-XX-DV-A-S
JP1: 2X07M
JP2: 1X03/90-S
JP3: 1X02-S
L1: 0402-C
LOGO2: OSHW_LOGO_FILLX0100-NT; OSHW_FILLX100_NOTEXT
PCIE-NORTH: PCIE-36-AXIOM
PCIE-SOUTH: PCIE-36-AXIOM
R1: 10k; 0402-B
R2: 1k; 0402-B
R3, R4, R5, R6, R7: 10k; 0402-C
R8: 0201-C
R9, R10, R11, R12, R13, R14: 75R; 0201-C
R15: 100R; 0201-C
U1: BR24G04NUX; DFN200X300X100-9N
U2: GS12241; UQFN40P600X400X100-41N
U3, U4: GS12281; UQFN40P600X400X100-41N
U5: DSC11XX-3.2X2.5; 3.2X2.5
X1, X2, X3: HDBNC; HDBNC_EDGE_2SIDE

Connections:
1V8: FB1.1, FB2.1, FB3.1, FB4.1, FB5.1, FB7.1, FB8.1, JM2.18
3V3: D1.A@1, D2.A@1, D3.A@1, D4.A@1, FB6.1, FB9.1, JM1.83, L1.1, R3.2
B14_L0: JM2.99, U5.1
B34_L20_N: JM1.76, R4.1
B34_L20_P: JM1.78, R5.1
B34_L24_N: JM1.80, R6.1
B34_L24_P: JM1.82, R7.1
BOOTMODE: JM2.100, JP3.1
DONE: D5.A@1, JM1.96, R3.1
GND: C1.2, C5.2, C6.2, C7.2, C8.2, C9.2, C10.2, C11.2, C12.2, C13.2, C14.2, C15.2, C16.2, C22.2, C23.2, C24.2, C25.2, C26.2, C27.2, C28.2, C29.2, C30.2, C31.2, C32.2, C33.2, C34.2, C40.2, C41.2, C42.2, C43.2, C44.2, C45.2, C46.2, C47.2, C48.2, C49.2, C50.2, C51.2, C52.2, C53.2, D5.C@1, JM1.5, JM1.6, JM1.11, JM1.12, JM1.17, JM1.18, JM1.23, JM1.24, JM1.29, JM1.30, JM1.47, JM1.48, JM1.66, JM1.84, JM1.98, JM1.100, JM1.F1, JM1.F2, JM2.17, JM2.35, JM2.36, JM2.72, JM2.83, JM2.90, JM2.F1, JM2.F2, JP2.1, JP3.2, PCIE-NORTH.A1, PCIE-NORTH.A4, PCIE-NORTH.A7, PCIE-NORTH.A10, PCIE-NORTH.A12, PCIE-NORTH.A15, PCIE-NORTH.A18, PCIE-NORTH.B15, PCIE-NORTH.B18, PCIE-SOUTH.A1, PCIE-SOUTH.A4, PCIE-SOUTH.A7, PCIE-SOUTH.A10, PCIE-SOUTH.A12, PCIE-SOUTH.A15, PCIE-SOUTH.A18, PCIE-SOUTH.B15, PCIE-SOUTH.B18, R2.2, R8.2, R9.2, R10.2, R11.2, R12.2, R13.2, R14.2, U1.1, U1.2, U1.3, U1.4, U1.EP, U2.1, U2.8, U2.14, U2.15, U2.19, U2.21, U2.28, U2.31, U2.37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
I2C_V: C1.1, PCIE-NORTH.B3, R1.1, U1.8
MGT_RX0_N: JM1.21, U2.27
MGT_RX0_P: JM1.19, U2.26
MGT_RX1_N: JM1.15, U2.23
MGT_RX1_P: JM1.13, U2.22
MGT_TX0_N: JM1.28, U4.6
MGT_TX0_P: JM1.26, U4.7
MGT_TX1_N: JM1.22, U3.6
MGT_TX1_P: JM1.20, U3.7
unnamed: D1.C@1, R4.2
unnamed: D2.C@1, R5.2
unnamed: D3.C@1, R6.2
unnamed: D4.C@1, R7.2
unnamed: C3.2, U2.40
unnamed: C3.1, U2.39
unnamed: C21.2, U3.40
unnamed: C21.1, U3.39
unnamed: C6.1, U2.30
unnamed: C5.1, U2.34
unnamed: C18.2, R9.1
unnamed: C18.1, U3.22
unnamed: C19.1, U3.23
unnamed: C19.2, R10.1
unnamed: C20.1, U3.26
unnamed: C20.2, R11.1
unnamed: C4.2, R8.1
unnamed: C4.1, U2.3
unnamed: C24.1, U3.30
unnamed: C23.1, U3.34
unnamed: C17.1, U3.27
unnamed: C22.1, U3.5
unnamed: C17.2, X2.1
unnamed: C2.2, U2.2
unnamed: C2.1, X1.1
unnamed: C35.1, U4.27
unnamed: C35.2, X3.1
unnamed: C39.2, U4.40
unnamed: C40.1, U4.5
unnamed: C41.1, U4.34
unnamed: C42.1, U4.30
unnamed: C38.2, R14.1
unnamed: C38.1, U4.26
unnamed: C37.2, R13.1
unnamed: C37.1, U4.23
unnamed: C36.1, U4.22
unnamed: C36.2, R12.1
unnamed: C39.1, U4.39
unnamed: R1.2, R2.1, U1.7
OUT_N: C55.1, R15.2, U5.5
OUT_P: C54.1, R15.1, U5.4
SCL: PCIE-NORTH.B2, U1.6
SDA: PCIE-NORTH.B1, U1.5
VCCO_4: C14.1, C15.1, C16.1, FB3.2, U2.24, U2.25
VCCO_8: C32.1, C33.1, C34.1, FB6.2, U3.24, U3.25
VCCO_9: C50.1, C51.1, C52.1, FB9.2, U4.24, U4.25
VCC_4: C11.1, C12.1, C13.1, FB2.2, U2.4, U2.35
VCC_8: C29.1, C30.1, C31.1, FB5.2, U3.4, U3.35
VCC_9: C47.1, C48.1, C49.1, FB8.2, U4.4, U4.35
VDD_4: C7.1, C8.1, C9.1, C10.1, FB1.2, U2.16, U2.20, U2.29
VDD_8: C25.1, C26.1, C27.1, C28.1, FB4.2, U3.16, U3.20, U3.29
VDD_9: C43.1, C44.1, C45.1, C46.1, FB7.2, U4.16, U4.20, U4.29
VIN: JM1.97, JM1.99, JP2.2
VXX: C53.1, L1.2, U5.6

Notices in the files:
boards/axiom_beta_main_board_v0.35.brd:
Copyright (C) 2015 Herbert Pötzl
Licensed under CERN OHL v.1.2
boards/axiom_beta_plugin_module_1xHDMI_v0.5.brd:
(C) 2015 H.Pötzl
CERN OHL v.1.2
boards/axiom_beta_plugin_module_TE0714_SDI_v0.10_r1.2.brd:
Copyright (C) 2017 Herbert Pötzl
parts and their libraries:
microbuilder: This work is placed in the public domain, and may be freely used for commercial and non-commercial work with the following conditions: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
